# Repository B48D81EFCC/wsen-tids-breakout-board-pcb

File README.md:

# Würth Elektronik WSEN-TIDS Breakout Board PCB
*KiCad project files for a breakout board using the Würth Elektronik WSEN-TIDS temperature sensor.*

## Overview
The breakout board simplifies integration of the **WSEN-TIDS temperature sensor** into your projects.  
The main goal of this PCB is to fit into stainless steel sleeve of around 5mm diameter.  

### JST SH connector pinout

| Pin # | Function |
|-------|----------|
| 1     | GND      |
| 2     | 3.3V     |
| 3     | SDA      |
| 4     | SCL      |

The pinout layout is widely used across different vendors of breakout boards with JST SH connector, allowing to use multiple different sensors on one bus more easily. Although the pin layout is (often) the same, each vendor uses their own brand names (e.g: STEMMA, μŠup)

> [!CAUTION]
> The design is not 5V compliant and 5V will destroy the sensor.  
> **Use 3.3V only.** 

---

# Additional resources
[Official WSEN-TIDS Product Page (Würth Elektronik Website)](https://www.we-online.com/de/components/products/WSEN-TIDS)

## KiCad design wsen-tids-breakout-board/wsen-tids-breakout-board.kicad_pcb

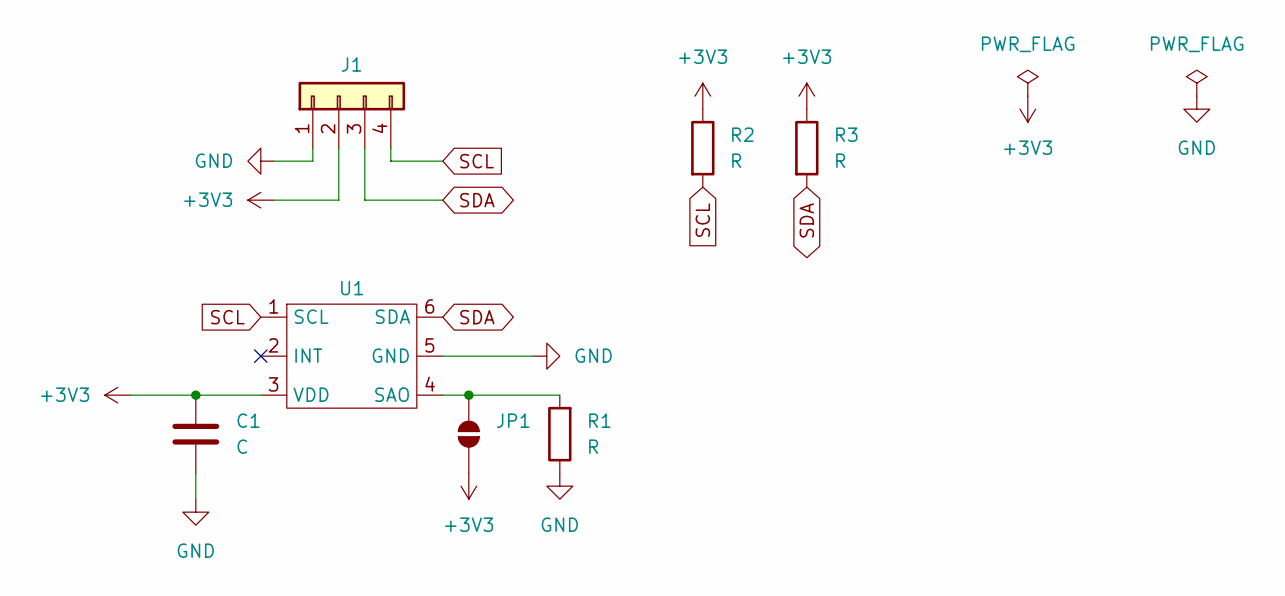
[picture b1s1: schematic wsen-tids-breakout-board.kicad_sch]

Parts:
C1: C; C_0402_1005Metric
J1: Conn_01x04; JST_SH_SM04B-SRSS-TB_1x04-1MP_P1.00mm_Horizontal
JP1: SolderJumper_2_Open; SolderJumper-2_P1.3mm_Open_RoundedPad1.0x1.5mm
R1, R2, R3: R; R_0402_1005Metric
U1: 2521020222501; U_Wurth_WSEN-TIDS_2521020222501; Part Number 2521020222501

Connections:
+3V3: C1.1, J1.2, JP1.1 (A), R2.1, R3.1, U1.3 (VDD)
GND: C1.2, J1.1, R1.1, U1.5 (GND)
unnamed: JP1.2 (B), R1.2, U1.4 (SAO)
SCL: J1.4, R2.2, U1.1 (SCL)
SDA: J1.3, R3.2, U1.6 (SDA)

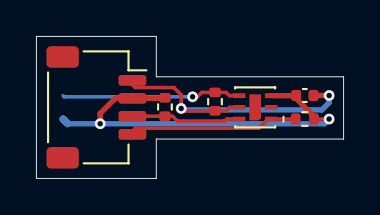
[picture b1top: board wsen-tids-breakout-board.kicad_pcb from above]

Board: 2 copper layers, 17.1 x 7.9 mm, 7 parts (1 on the bottom side), 5 nets.

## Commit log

2025-11-12 Initial commit of project files
2025-11-12 README file updated
2025-11-12 Update image references updaed
2025-11-12 Images added
2025-11-12 Fixed wrong image references
